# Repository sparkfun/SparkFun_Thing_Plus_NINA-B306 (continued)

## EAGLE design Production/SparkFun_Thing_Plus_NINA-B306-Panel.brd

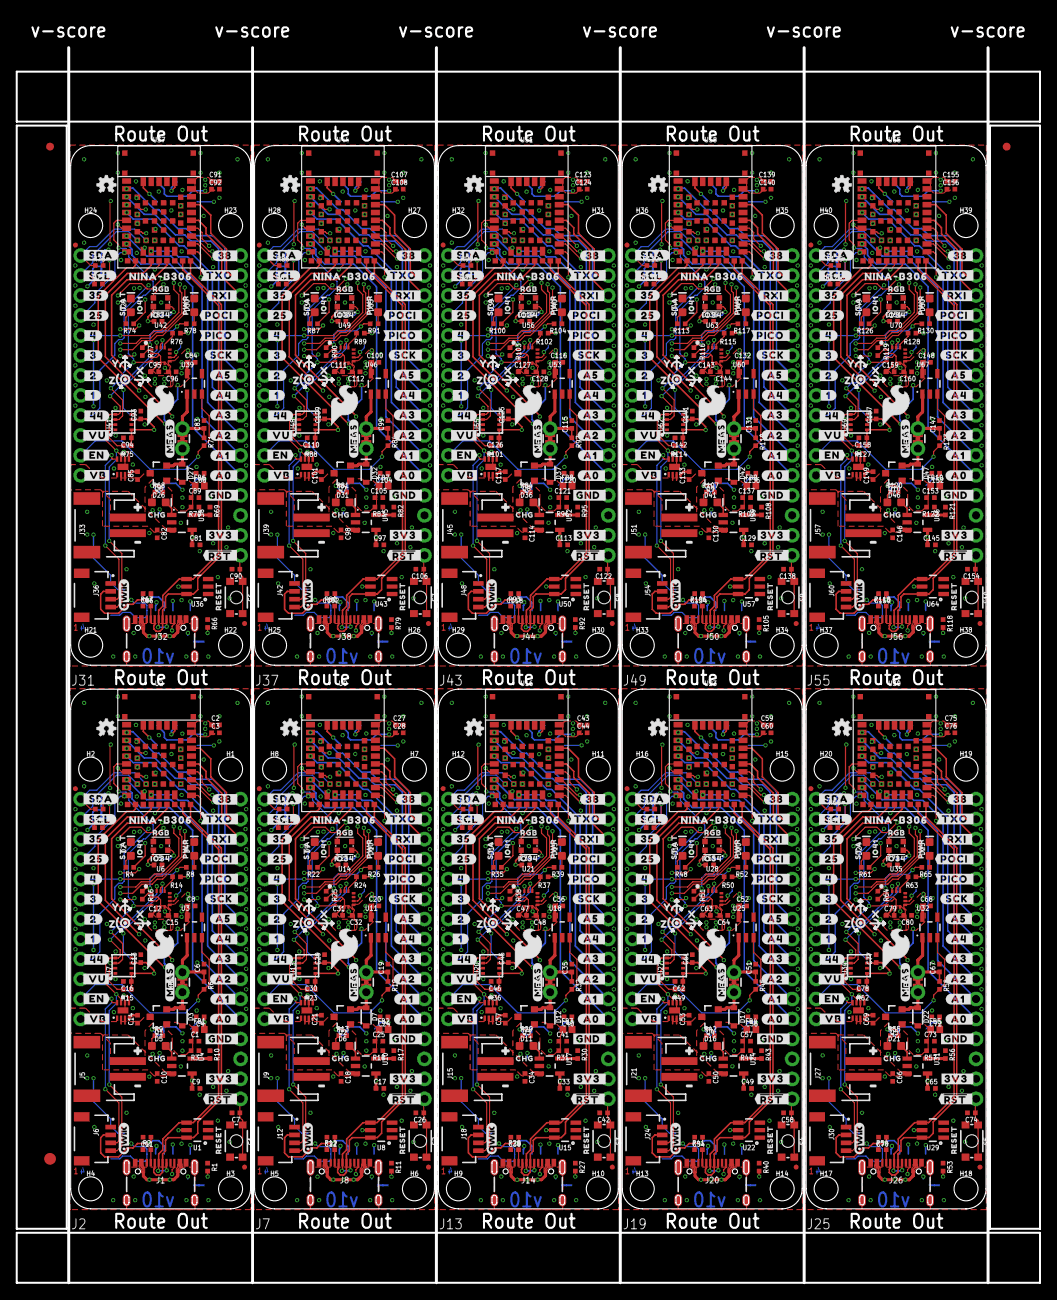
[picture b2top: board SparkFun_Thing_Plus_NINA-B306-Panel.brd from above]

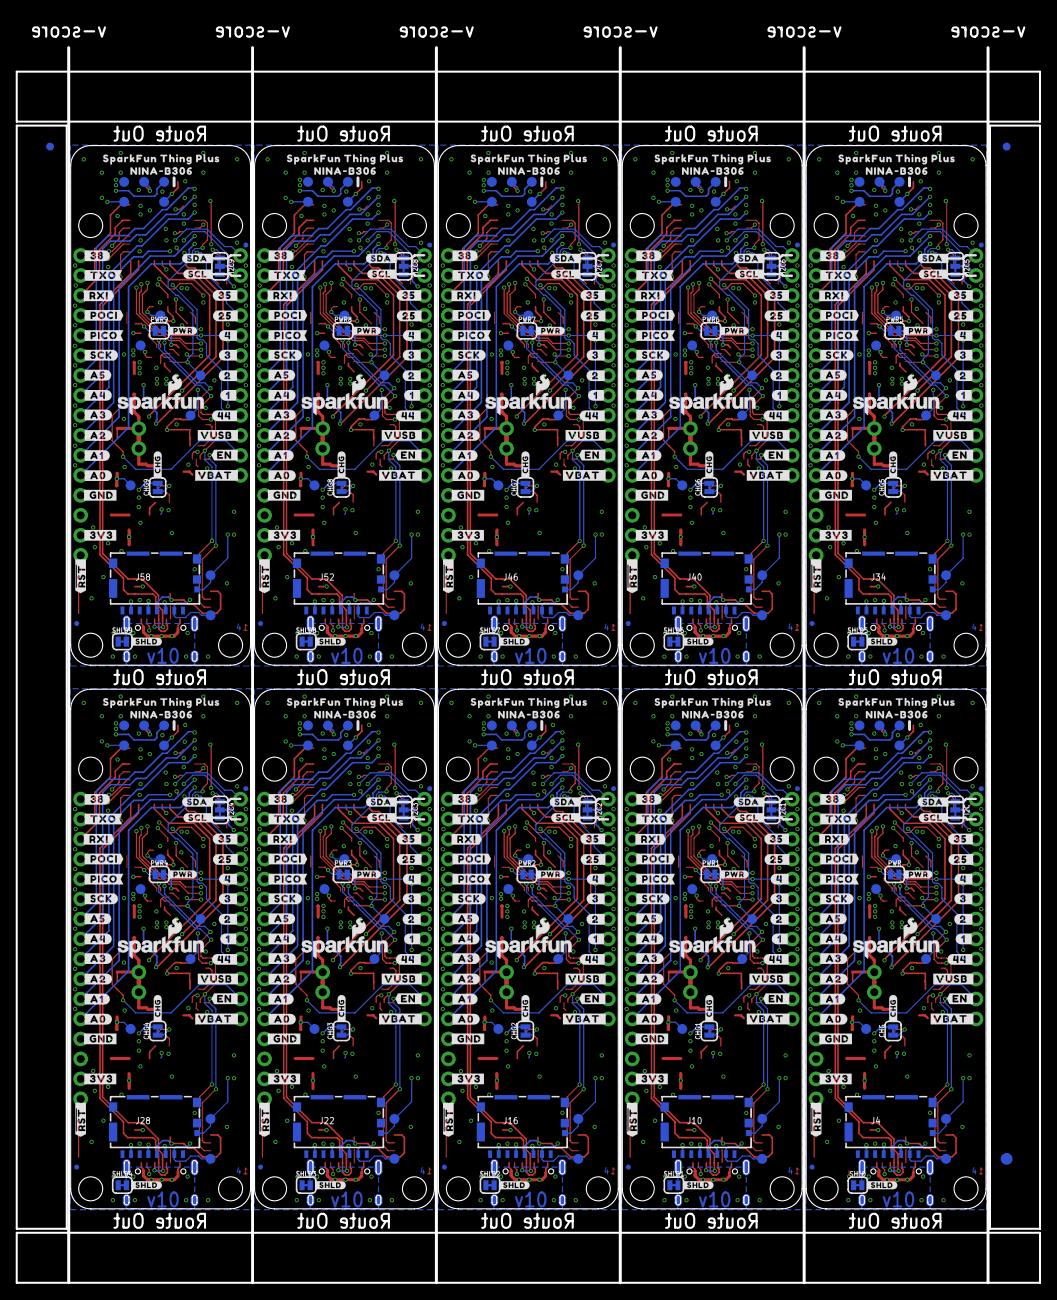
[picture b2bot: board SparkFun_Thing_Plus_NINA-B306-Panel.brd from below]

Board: 4 copper layers, 130.0 x 157.0 mm, 1506 parts (493 on the bottom side), 570 nets.

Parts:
C1, C4, C24, C25, C40, C41, C56, C57, C72, C73, C88, C89, C104, C105, C120, C121, C136, C137, C152, C153: 1.0nF; 0402-TIGHT
C2, C3, C5, C7, C12, C13, C14, C15, C16, C21, C23, C26, C27, C28, C29, C30, C31, C32, C37, C39, C42, C43, C44, C45, C46, C47, C48, C53, C55, C58, C59, C60, C61, C62, C63, C64, C69, C71, C74, C75, C76, C77, C78, C79, C80, C85, C87, C90, C91, C92, C93, C94, C95, C96, C101, C103, C106, C107, C108, C109, C110, C111, C112, C117, C119, C122, C123, C124, C125, C126, C127, C128, C133, C135, C138, C139, C140, C141, C142, C143, C144, C149, C151, C154, C155, C156, C157, C158, C159, C160: 0.1uF; 0402-TIGHT
C6, C19, C35, C51, C67, C83, C99, C115, C131, C147: 1.0uF; 0402-TIGHT
C8, C20, C36, C52, C68, C84, C100, C116, C132, C148: 2.2uF; 0402-TIGHT
C9, C10, C17, C18, C33, C34, C49, C50, C65, C66, C81, C82, C97, C98, C113, C114, C129, C130, C145, C146: 4.7uF; 0402-TIGHT
C11, C22, C38, C54, C70, C86, C102, C118, C134, C150: 10uF; 0402-TIGHT
CHG, CHG1, CHG2, CHG3, CHG4, CHG5, CHG6, CHG7, CHG8, CHG9: JUMPER-SMT_2_NC_TRACE_SILK; SMT-JUMPER_2_NC_TRACE_SILK
D1, D8, D13, D18, D23, D28, D33, D38, D43, D48: WS2812; WS2812-2020
D2, D9, D14, D19, D24, D29, D34, D39, D44, D49: BLUE; LED-0603
D3, D7, D12, D17, D22, D27, D32, D37, D42, D47: 3A/10V/280mV; SOD-323
D4, D10, D15, D20, D25, D30, D35, D40, D45, D50: RED; LED-0603
D5, D6, D11, D16, D21, D26, D31, D36, D41, D46: Yellow; LED-0603
E$1, E$2, E$3, E$4: FIDUCIAL-1X2
E$5, E$6: FIDUCIAL-1.5X3
FB1, FB2, FB3, FB4, FB5, FB6, FB7, FB8, FB9, FB10: 120Ω; 0402
FD1, FD2, FD3, FD4, FD5, FD6, FD7, FD8, FD9, FD10, FD11, FD12, FD13, FD14, FD15, FD16, FD17, FD18, FD19, FD20, FD21, FD22, FD23, FD24, FD25, FD26, FD27, FD28, FD29, FD30, FD31, FD32, FD33, FD34, FD35, FD36, FD37, FD38, FD39, FD40: FIDUCIALUFIDUCIAL; FIDUCIAL-MICRO
H1, H2, H3, H4, H5, H6, H7, H8, H9, H10, H11, H12, H13, H14, H15, H16, H17, H18, H19, H20, H21, H22, H23, H24, H25, H26, H27, H28, H29, H30, H31, H32, H33, H34, H35, H36, H37, H38, H39, H40: STAND-OFFTIGHT; STAND-OFF-TIGHT
I2C, I2C1, I2C2, I2C3, I2C4, I2C5, I2C6, I2C7, I2C8, I2C9: JUMPER-SMT_3_2-NC_TRACE_SILK; SMT-JUMPER_3_2-NC_TRACE_SILK
J1, J8, J14, J20, J26, J32, J38, J44, J50, J56: USB-C; USB-C-16P-4LAYER-ISOLATED
J2, J7, J13, J19, J25, J31, J37, J43, J49, J55: THING_PLUS_LOGICAL; THING_PLUS
J3, J11, J17, J23, J29, J35, J41, J47, J53, J59: CONN_03X2_NO4; PAD_05_03X2_TP_NO4
J4, J10, J16, J22, J28, J34, J40, J46, J52, J58: MICRO-SDFRICTION; MICROSD_TINY
J5, J9, J15, J21, J27, J33, J39, J45, J51, J57: JST-2-SMD
J6, J12, J18, J24, J30, J36, J42, J48, J54, J60: QWIIC_RA; JST04_1MM_RA
LOGO1, LOGO6, LOGO11, LOGO16, LOGO21, LOGO26, LOGO31, LOGO36, LOGO41, LOGO46: SFE_LOGO_NAME_FLAME.1_INCH; SFE_LOGO_NAME_FLAME_.1
LOGO2, LOGO10, LOGO15, LOGO20, LOGO25, LOGO30, LOGO35, LOGO40, LOGO45, LOGO50: FOUR_LAYER_WARNING
LOGO3, LOGO8, LOGO13, LOGO18, LOGO23, LOGO28, LOGO33, LOGO38, LOGO43, LOGO48: SPECIAL_INSTRUCTIONS-ORDERING; ORDERING_INSTRUCTIONS
LOGO4, LOGO9, LOGO14, LOGO19, LOGO24, LOGO29, LOGO34, LOGO39, LOGO44, LOGO49: QWIIC_LOGO_4MM; QWIIC_4MM
LOGO5, LOGO7, LOGO12, LOGO17, LOGO22, LOGO27, LOGO32, LOGO37, LOGO42, LOGO47: OSHW-LOGOMINI; OSHW-LOGO-MINI
MEAS, MEAS1, MEAS2, MEAS3, MEAS4, MEAS5, MEAS6, MEAS7, MEAS8, MEAS9: JUMPER-COMBO_2_NC_TRACE; COMBO-JUMPER_2_NC_TRACE
PWR, PWR1, PWR2, PWR3, PWR4, PWR5, PWR6, PWR7, PWR8, PWR9: JUMPER-SMT_2_NC_TRACE_SILK; SMT-JUMPER_2_NC_TRACE_SILK
Q1, Q2, Q3, Q4, Q5, Q6, Q7, Q8, Q9, Q10: 20V/4.2A/52mΩ/1.4W; SOT23-3
R1, R2, R11, R12, R27, R28, R40, R41, R53, R54, R66, R67, R79, R80, R92, R93, R105, R106, R118, R119: 5.1k; 0402-TIGHT
R3, R6, R14, R15, R16, R18, R19, R23, R24, R25, R31, R32, R36, R37, R38, R44, R45, R49, R50, R51, R57, R58, R62, R63, R64, R70, R71, R75, R76, R77, R83, R84, R88, R89, R90, R96, R97, R101, R102, R103, R109, R110, R114, R115, R116, R122, R123, R127, R128, R129: 10k; 0402-TIGHT
R4, R5, R7, R20, R21, R22, R33, R34, R35, R46, R47, R48, R59, R60, R61, R72, R73, R74, R85, R86, R87, R98, R99, R100, R111, R112, R113, R124, R125, R126: 2.2k; 0402-TIGHT
R8, R26, R39, R52, R65, R78, R91, R104, R117, R130: 1k; 0402-TIGHT
R9, R13, R29, R42, R55, R68, R81, R94, R107, R120: 4.7k; 0402-TIGHT
R10, R17, R30, R43, R56, R69, R82, R95, R108, R121: 2.0K; 0402-TIGHT
S1, S2, S3, S4, S5, S6, S7, S8, S9, S10: Reset; TACTILE_SWITCH_SMD_4.6X2.8MM
SHLD, SHLD1, SHLD2, SHLD3, SHLD4, SHLD5, SHLD6, SHLD7, SHLD8, SHLD9: SMT-JUMPER_2_NC_TRACE_SILK
TP1, TP2, TP3, TP4, TP5, TP6, TP7, TP8, TP9, TP10, TP11, TP12, TP13, TP14, TP15, TP16, TP17, TP18, TP19, TP20, TP21, TP22, TP23, TP24, TP25, TP26, TP27, TP28, TP29, TP30, TP31, TP32, TP33, TP34, TP35, TP36, TP37, TP38, TP39, TP40, TP41, TP42, TP43, TP44, TP45, TP46, TP47, TP48, TP49, TP50, TP51, TP52, TP53, TP54, TP55, TP56, TP57, TP58, TP59, TP60, TP61, TP62, TP63, TP64, TP65, TP66, TP67, TP68, TP69, TP70: TEST-POINT3X5; PAD.03X.05
U1, U8, U15, U22, U29, U36, U43, U50, U57, U64: ESD Diode; SOT-23-6
U2, U9, U16, U23, U30, U37, U44, U51, U58, U65: U-BLOX_NINA_B306; NINA_B306
U3, U11, U18, U25, U32, U39, U46, U53, U60, U67: XC6222B331MR-G; SOT23-5
U4, U10, U17, U24, U31, U38, U45, U52, U59, U66: MCP73831; SOT23-5
U5, U12, U19, U26, U33, U40, U47, U54, U61, U68: MAX17048; DFN-8
U6, U14, U21, U28, U35, U42, U49, U56, U63, U70: ISM330DHCX; LGA-14L
U7, U13, U20, U27, U34, U41, U48, U55, U62, U69: BME280; LGA-8-2.5X2.5
U$1, U$15, U$151, U$226, U$301, U$376, U$451, U$526, U$601, U$676: SFE_LOGO_FLAME_STOP_.1
U$2, U$77, U$152, U$227, U$302, U$377, U$452, U$527, U$602, U$677: SFE_LOGO_FLAME_.2
U$3, U$142, U$217, U$292, U$367, U$442, U$517, U$592, U$667, U$742: #_VU#0
U$4, U$78, U$153, U$228, U$303, U$378, U$453, U$528, U$603, U$678: #_EN#47
U$5, U$143, U$218, U$293, U$368, U$443, U$518, U$593, U$668, U$743: #3V3_#0
U$6, U$79, U$154, U$229, U$304, U$379, U$454, U$529, U$604, U$679: #_44#49
U$7, U$80, U$155, U$230, U$305, U$380, U$455, U$530, U$605, U$680: #_1#49
U$8, U$81, U$156, U$231, U$306, U$381, U$456, U$531, U$606, U$681: #_2#49
U$9, U$82, U$157, U$232, U$307, U$382, U$457, U$532, U$607, U$682: #_3#49
U$10, U$83, U$158, U$233, U$308, U$383, U$458, U$533, U$608, U$683: #_4#49
U$11, U$84, U$159, U$234, U$309, U$384, U$459, U$534, U$609, U$684: #_25#49
U$12, U$140, U$215, U$290, U$365, U$440, U$515, U$590, U$665, U$740: #_35#0
U$13, U$85, U$160, U$235, U$310, U$385, U$460, U$535, U$610, U$685: #_SCL#49
U$14, U$144, U$219, U$294, U$369, U$444, U$519, U$594, U$669, U$744: RESET0
U$16, U$86, U$161, U$236, U$311, U$386, U$461, U$536, U$611, U$686: #GND_#53
U$17, U$87, U$162, U$237, U$312, U$387, U$462, U$537, U$612, U$687: #A0_#54
U$18, U$88, U$163, U$238, U$313, U$388, U$463, U$538, U$613, U$688: #A1_#54
U$19, U$89, U$164, U$239, U$314, U$389, U$464, U$539, U$614, U$689: #A2_#54
U$20, U$90, U$165, U$240, U$315, U$390, U$465, U$540, U$615, U$690: #A3_#54
U$21, U$91, U$166, U$241, U$316, U$391, U$466, U$541, U$616, U$691: #A4_#54
U$22, U$92, U$167, U$242, U$317, U$392, U$467, U$542, U$617, U$692: #A5_#54
U$23, U$93, U$168, U$243, U$318, U$393, U$468, U$543, U$618, U$693: #SCK_#54
U$24, U$97, U$172, U$247, U$322, U$397, U$472, U$547, U$622, U$697: #PICO_#60
U$25, U$98, U$173, U$248, U$323, U$398, U$473, U$548, U$623, U$698: #POCI_#61
U$26, U$94, U$169, U$244, U$319, U$394, U$469, U$544, U$619, U$694: #TXO_#57
U$27, U$95, U$170, U$245, U$320, U$395, U$470, U$545, U$620, U$695: #RXI_#59
U$28, U$96, U$171, U$246, U$321, U$396, U$471, U$546, U$621, U$696: #38_#60
U$29, U$99, U$174, U$249, U$324, U$399, U$474, U$549, U$624, U$699: #_SDA#68
U$30, U$127, U$202, U$277, U$352, U$427, U$502, U$577, U$652, U$727: #_CHG#30707
U$31, U$147, U$222, U$297, U$372, U$447, U$522, U$597, U$672, U$747: #_3V3#0
U$32, U$100, U$175, U$250, U$325, U$400, U$475, U$550, U$625, U$700: #_GND#70
U$33, U$101, U$176, U$251, U$326, U$401, U$476, U$551, U$626, U$701: #_A0#71
U$34, U$102, U$177, U$252, U$327, U$402, U$477, U$552, U$627, U$702: #_A1#71
U$35, U$103, U$178, U$253, U$328, U$403, U$478, U$553, U$628, U$703: #_A2#71
U$36, U$104, U$179, U$254, U$329, U$404, U$479, U$554, U$629, U$704: #_A3#71
U$37, U$105, U$180, U$255, U$330, U$405, U$480, U$555, U$630, U$705: #_A4#71
U$38, U$106, U$181, U$256, U$331, U$406, U$481, U$556, U$631, U$706: #_A5#71
U$39, U$107, U$182, U$257, U$332, U$407, U$482, U$557, U$632, U$707: #_SCK#71
U$40, U$108, U$183, U$258, U$333, U$408, U$483, U$558, U$633, U$708: #_PICO#72
U$41, U$109, U$184, U$259, U$334, U$409, U$484, U$559, U$634, U$709: #_POCI#73
U$42, U$110, U$185, U$260, U$335, U$410, U$485, U$560, U$635, U$710: #_TXO#74
U$43, U$111, U$186, U$261, U$336, U$411, U$486, U$561, U$636, U$711: #_RXI#75
U$44, U$112, U$187, U$262, U$337, U$412, U$487, U$562, U$637, U$712: #_38#76
U$45, U$139, U$214, U$289, U$364, U$439, U$514, U$589, U$664, U$739: #35_#0
U$46, U$113, U$188, U$263, U$338, U$413, U$488, U$563, U$638, U$713: #25_#79
U$47, U$114, U$189, U$264, U$339, U$414, U$489, U$564, U$639, U$714: #4_#79
U$48, U$115, U$190, U$265, U$340, U$415, U$490, U$565, U$640, U$715: #3_#79
U$49, U$116, U$191, U$266, U$341, U$416, U$491, U$566, U$641, U$716: #2_#79
U$50, U$117, U$192, U$267, U$342, U$417, U$492, U$567, U$642, U$717: #1_#79
U$51, U$118, U$193, U$268, U$343, U$418, U$493, U$568, U$643, U$718: #44_#79
U$52, U$146, U$221, U$296, U$371, U$446, U$521, U$596, U$671, U$746: #VBAT_#0
U$53, U$119, U$194, U$269, U$344, U$419, U$494, U$569, U$644, U$719: #EN_#80
U$54, U$74, U$138, U$148, U$213, U$223, U$288, U$298, U$363, U$373, U$438, U$448, U$513, U$523, U$588, U$598, U$663, U$673, U$738, U$748: ##RST#_#0
U$55, U$120, U$195, U$270, U$345, U$420, U$495, U$570, U$645, U$720: #SDA_#82
U$56, U$121, U$196, U$271, U$346, U$421, U$496, U$571, U$646, U$721: #SCL_#85
U$57, U$122, U$197, U$272, U$347, U$422, U$497, U$572, U$647, U$722: #_PWR#90
U$58, U$145, U$220, U$295, U$370, U$445, U$520, U$595, U$670, U$745: #VUSB_#0
U$59, U$123, U$198, U$273, U$348, U$423, U$498, U$573, U$648, U$723: #_SHLD#93
U$60, U$124, U$199, U$274, U$349, U$424, U$499, U$574, U$649, U$724: SPARKFUN_THING_PLUS96
U$61, U$125, U$200, U$275, U$350, U$425, U$500, U$575, U$650, U$725: NINA#B30697
U$62, U$126, U$201, U$276, U$351, U$426, U$501, U$576, U$651, U$726: #MEAS#30701
U$63, U$141, U$216, U$291, U$366, U$441, U$516, U$591, U$666, U$741: #_VB#0
U$64, U$128, U$203, U$278, U$353, U$428, U$503, U$578, U$653, U$728: RGB30710
U$65, U$129, U$204, U$279, U$354, U$429, U$504, U$579, U$654, U$729: STAT30711
U$66, U$130, U$205, U$280, U$355, U$430, U$505, U$580, U$655, U$730: PWR30712
U$67, U$131, U$206, U$281, U$356, U$431, U$506, U$581, U$656, U$731: NINA#B30630713
U$68, U$132, U$207, U$282, U$357, U$432, U$507, U$582, U$657, U$732: X2114
U$69, U$133, U$208, U$283, U$358, U$433, U$508, U$583, U$658, U$733: Y2115
U$70, U$134, U$209, U$284, U$359, U$434, U$509, U$584, U$659, U$734: Z2116
U$71, U$135, U$210, U$285, U$360, U$435, U$510, U$585, U$660, U$735: IO414130630715
U$72, U$136, U$211, U$286, U$361, U$436, U$511, U$586, U$661, U$736: IO34414130630716
U$73, U$137, U$212, U$287, U$362, U$437, U$512, U$587, U$662, U$737: CHG0
U$75, U$149, U$224, U$299, U$374, U$449, U$524, U$599, U$674, U$749: #3
U$76, U$150, U$225, U$300, U$375, U$450, U$525, U$600, U$675, U$750: #4

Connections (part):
3.3V: C2.1, C3.1, C5.1, C8.1, C11.1, C12.1, C13.1, C15.1, C16.1, D1.VCC, I2C.2, J2.27, J3.1, J4.4, J6.2, PWR.2, R14.1, R15.1, R16.1, U2.9, U2.10, U3.5, U6.P5, U6.P8, U7.6, U7.8
3.3V1: C20.1, C22.1, C23.1, C27.1, C28.1, C29.1, C30.1, C31.1, C32.1, D8.VCC, I2C1.2, J7.27, J10.4, J11.1, J12.2, PWR1.2, R23.1, R24.1, R25.1, U9.9, U9.10, U11.5, U13.6, U13.8, U14.P5, U14.P8
3.3V2: C36.1, C38.1, C39.1, C43.1, C44.1, C45.1, C46.1, C47.1, C48.1, D13.VCC, I2C2.2, J13.27, J16.4, J17.1, J18.2, PWR2.2, R36.1, R37.1, R38.1, U16.9, U16.10, U18.5, U20.6, U20.8, U21.P5, U21.P8
3.3V3: C52.1, C54.1, C55.1, C59.1, C60.1, C61.1, C62.1, C63.1, C64.1, D18.VCC, I2C3.2, J19.27, J22.4, J23.1, J24.2, PWR3.2, R49.1, R50.1, R51.1, U23.9, U23.10, U25.5, U27.6, U27.8, U28.P5, U28.P8
3.3V4: C68.1, C70.1, C71.1, C75.1, C76.1, C77.1, C78.1, C79.1, C80.1, D23.VCC, I2C4.2, J25.27, J28.4, J29.1, J30.2, PWR4.2, R62.1, R63.1, R64.1, U30.9, U30.10, U32.5, U34.6, U34.8, U35.P5, U35.P8
3.3V5: C84.1, C86.1, C87.1, C91.1, C92.1, C93.1, C94.1, C95.1, C96.1, D28.VCC, I2C5.2, J31.27, J34.4, J35.1, J36.2, PWR5.2, R75.1, R76.1, R77.1, U37.9, U37.10, U39.5, U41.6, U41.8, U42.P5, U42.P8
3.3V6: C100.1, C102.1, C103.1, C107.1, C108.1, C109.1, C110.1, C111.1, C112.1, D33.VCC, I2C6.2, J37.27, J40.4, J41.1, J42.2, PWR6.2, R88.1, R89.1, R90.1, U44.9, U44.10, U46.5, U48.6, U48.8, U49.P5, U49.P8
3.3V7: C116.1, C118.1, C119.1, C123.1, C124.1, C125.1, C126.1, C127.1, C128.1, D38.VCC, I2C7.2, J43.27, J46.4, J47.1, J48.2, PWR7.2, R101.1, R102.1, R103.1, U51.9, U51.10, U53.5, U55.6, U55.8, U56.P5, U56.P8
3.3V8: C132.1, C134.1, C135.1, C139.1, C140.1, C141.1, C142.1, C143.1, C144.1, D43.VCC, I2C8.2, J49.27, J52.4, J53.1, J54.2, PWR8.2, R114.1, R115.1, R116.1, U58.9, U58.10, U60.5, U62.6, U62.8, U63.P5, U63.P8
3.3V9: C148.1, C150.1, C151.1, C155.1, C156.1, C157.1, C158.1, C159.1, C160.1, D48.VCC, I2C9.2, J55.27, J58.4, J59.1, J60.2, PWR9.2, R127.1, R128.1, R129.1, U65.9, U65.10, U67.5, U69.6, U69.8, U70.P5, U70.P8
!RESET!: C7.1, J2.28, J3.6, S1.3, S1.4, U2.19
!RESET!1: C26.1, J7.28, J11.6, S2.3, S2.4, U9.19
!RESET!2: C42.1, J13.28, J17.6, S3.3, S3.4, U16.19
!RESET!3: C58.1, J19.28, J23.6, S4.3, S4.4, U23.19
!RESET!4: C74.1, J25.28, J29.6, S5.3, S5.4, U30.19
!RESET!5: C90.1, J31.28, J35.6, S6.3, S6.4, U37.19
!RESET!6: C106.1, J37.28, J41.6, S7.3, S7.4, U44.19
!RESET!7: C122.1, J43.28, J47.6, S8.3, S8.4, U51.19
!RESET!8: C138.1, J49.28, J53.6, S9.3, S9.4, U58.19
!RESET!9: C154.1, J55.28, J59.6, S10.3, S10.4, U65.19
EN: J2.11, R6.2, U3.3
EN1: J7.11, R19.2, U11.3
EN2: J13.11, R32.2, U18.3
EN3: J19.11, R45.2, U25.3
EN4: J25.11, R58.2, U32.3
EN5: J31.11, R71.2, U39.3
EN6: J37.11, R84.2, U46.3
EN7: J43.11, R97.2, U53.3
EN8: J49.11, R110.2, U60.3
EN9: J55.11, R123.2, U67.3
GND: C1.2, C2.2, C3.2, C4.2, C5.2, C6.2, C7.2, C8.2, C9.2, C10.2, C11.2, C12.2, C13.2, C14.2, C15.2, C16.2, D1.GND, D2.C, D4.C, J1.GND, J1.GND2, J2.25, J3.5, J4.6, J4.GND1, J4.GND2, J4.GND3, J4.GND4, J4.GND5, J4.GND6, J5.1, J6.1, R1.1, R2.1, R3.1, R10.1, S1.1, S1.2, SHLD.1, U1.2, U2.6, U2.12, U2.14, U2.26, U2.30, U2.53, U2.56, U2.57, U2.58, U2.59, U2.60, U2.61, U2.62, U2.63, U2.64, U2.65, U2.66, U2.67, U2.68, U2.69, U2.70, U2.71, U3.2, U4.2, U5.1, U5.4, U5.6, U5.9, U6.P2, U6.P3, U6.P6, U6.P7, U7.1, U7.5, U7.7
GND1: C17.2, C18.2, C19.2, C20.2, C21.2, C22.2, C23.2, C24.2, C25.2, C26.2, C27.2, C28.2, C29.2, C30.2, C31.2, C32.2, D8.GND, D9.C, D10.C, J7.25, J8.GND, J8.GND2, J9.1, J10.6, J10.GND1, J10.GND2, J10.GND3, J10.GND4, J10.GND5, J10.GND6, J11.5, J12.1, R11.1, R12.1, R17.1, R18.1, S2.1, S2.2, SHLD1.1, U8.2, U9.6, U9.12, U9.14, U9.26, U9.30, U9.53, U9.56, U9.57, U9.58, U9.59, U9.60, U9.61, U9.62, U9.63, U9.64, U9.65, U9.66, U9.67, U9.68, U9.69, U9.70, U9.71, U10.2, U11.2, U12.1, U12.4, U12.6, U12.9, U13.1, U13.5, U13.7, U14.P2, U14.P3, U14.P6, U14.P7
GND2: C33.2, C34.2, C35.2, C36.2, C37.2, C38.2, C39.2, C40.2, C41.2, C42.2, C43.2, C44.2, C45.2, C46.2, C47.2, C48.2, D13.GND, D14.C, D15.C, J13.25, J14.GND, J14.GND2, J15.1, J16.6, J16.GND1, J16.GND2, J16.GND3, J16.GND4, J16.GND5, J16.GND6, J17.5, J18.1, R27.1, R28.1, R30.1, R31.1, S3.1, S3.2, SHLD2.1, U15.2, U16.6, U16.12, U16.14, U16.26, U16.30, U16.53, U16.56, U16.57, U16.58, U16.59, U16.60, U16.61, U16.62, U16.63, U16.64, U16.65, U16.66, U16.67, U16.68, U16.69, U16.70, U16.71, U17.2, U18.2, U19.1, U19.4, U19.6, U19.9, U20.1, U20.5, U20.7, U21.P2, U21.P3, U21.P6, U21.P7
GND3: C49.2, C50.2, C51.2, C52.2, C53.2, C54.2, C55.2, C56.2, C57.2, C58.2, C59.2, C60.2, C61.2, C62.2, C63.2, C64.2, D18.GND, D19.C, D20.C, J19.25, J20.GND, J20.GND2, J21.1, J22.6, J22.GND1, J22.GND2, J22.GND3, J22.GND4, J22.GND5, J22.GND6, J23.5, J24.1, R40.1, R41.1, R43.1, R44.1, S4.1, S4.2, SHLD3.1, U22.2, U23.6, U23.12, U23.14, U23.26, U23.30, U23.53, U23.56, U23.57, U23.58, U23.59, U23.60, U23.61, U23.62, U23.63, U23.64, U23.65, U23.66, U23.67, U23.68, U23.69, U23.70, U23.71, U24.2, U25.2, U26.1, U26.4, U26.6, U26.9, U27.1, U27.5, U27.7, U28.P2, U28.P3, U28.P6, U28.P7
GND4: C65.2, C66.2, C67.2, C68.2, C69.2, C70.2, C71.2, C72.2, C73.2, C74.2, C75.2, C76.2, C77.2, C78.2, C79.2, C80.2, D23.GND, D24.C, D25.C, J25.25, J26.GND, J26.GND2, J27.1, J28.6, J28.GND1, J28.GND2, J28.GND3, J28.GND4, J28.GND5, J28.GND6, J29.5, J30.1, R53.1, R54.1, R56.1, R57.1, S5.1, S5.2, SHLD4.1, U29.2, U30.6, U30.12, U30.14, U30.26, U30.30, U30.53, U30.56, U30.57, U30.58, U30.59, U30.60, U30.61, U30.62, U30.63, U30.64, U30.65, U30.66, U30.67, U30.68, U30.69, U30.70, U30.71, U31.2, U32.2, U33.1, U33.4, U33.6, U33.9, U34.1, U34.5, U34.7, U35.P2, U35.P3, U35.P6, U35.P7
GND5: C81.2, C82.2, C83.2, C84.2, C85.2, C86.2, C87.2, C88.2, C89.2, C90.2, C91.2, C92.2, C93.2, C94.2, C95.2, C96.2, D28.GND, D29.C, D30.C, J31.25, J32.GND, J32.GND2, J33.1, J34.6, J34.GND1, J34.GND2, J34.GND3, J34.GND4, J34.GND5, J34.GND6, J35.5, J36.1, R66.1, R67.1, R69.1, R70.1, S6.1, S6.2, SHLD5.1, U36.2, U37.6, U37.12, U37.14, U37.26, U37.30, U37.53, U37.56, U37.57, U37.58, U37.59, U37.60, U37.61, U37.62, U37.63, U37.64, U37.65, U37.66, U37.67, U37.68, U37.69, U37.70, U37.71, U38.2, U39.2, U40.1, U40.4, U40.6, U40.9, U41.1, U41.5, U41.7, U42.P2, U42.P3, U42.P6, U42.P7
GND6: C97.2, C98.2, C99.2, C100.2, C101.2, C102.2, C103.2, C104.2, C105.2, C106.2, C107.2, C108.2, C109.2, C110.2, C111.2, C112.2, D33.GND, D34.C, D35.C, J37.25, J38.GND, J38.GND2, J39.1, J40.6, J40.GND1, J40.GND2, J40.GND3, J40.GND4, J40.GND5, J40.GND6, J41.5, J42.1, R79.1, R80.1, R82.1, R83.1, S7.1, S7.2, SHLD6.1, U43.2, U44.6, U44.12, U44.14, U44.26, U44.30, U44.53, U44.56, U44.57, U44.58, U44.59, U44.60, U44.61, U44.62, U44.63, U44.64, U44.65, U44.66, U44.67, U44.68, U44.69, U44.70, U44.71, U45.2, U46.2, U47.1, U47.4, U47.6, U47.9, U48.1, U48.5, U48.7, U49.P2, U49.P3, U49.P6, U49.P7
GND7: C113.2, C114.2, C115.2, C116.2, C117.2, C118.2, C119.2, C120.2, C121.2, C122.2, C123.2, C124.2, C125.2, C126.2, C127.2, C128.2, D38.GND, D39.C, D40.C, J43.25, J44.GND, J44.GND2, J45.1, J46.6, J46.GND1, J46.GND2, J46.GND3, J46.GND4, J46.GND5, J46.GND6, J47.5, J48.1, R92.1, R93.1, R95.1, R96.1, S8.1, S8.2, SHLD7.1, U50.2, U51.6, U51.12, U51.14, U51.26, U51.30, U51.53, U51.56, U51.57, U51.58, U51.59, U51.60, U51.61, U51.62, U51.63, U51.64, U51.65, U51.66, U51.67, U51.68, U51.69, U51.70, U51.71, U52.2, U53.2, U54.1, U54.4, U54.6, U54.9, U55.1, U55.5, U55.7, U56.P2, U56.P3, U56.P6, U56.P7
GND8: C129.2, C130.2, C131.2, C132.2, C133.2, C134.2, C135.2, C136.2, C137.2, C138.2, C139.2, C140.2, C141.2, C142.2, C143.2, C144.2, D43.GND, D44.C, D45.C, J49.25, J50.GND, J50.GND2, J51.1, J52.6, J52.GND1, J52.GND2, J52.GND3, J52.GND4, J52.GND5, J52.GND6, J53.5, J54.1, R105.1, R106.1, R108.1, R109.1, S9.1, S9.2, SHLD8.1, U57.2, U58.6, U58.12, U58.14, U58.26, U58.30, U58.53, U58.56, U58.57, U58.58, U58.59, U58.60, U58.61, U58.62, U58.63, U58.64, U58.65, U58.66, U58.67, U58.68, U58.69, U58.70, U58.71, U59.2, U60.2, U61.1, U61.4, U61.6, U61.9, U62.1, U62.5, U62.7, U63.P2, U63.P3, U63.P6, U63.P7
GND9: C145.2, C146.2, C147.2, C148.2, C149.2, C150.2, C151.2, C152.2, C153.2, C154.2, C155.2, C156.2, C157.2, C158.2, C159.2, C160.2, D48.GND, D49.C, D50.C, J55.25, J56.GND, J56.GND2, J57.1, J58.6, J58.GND1, J58.GND2, J58.GND3, J58.GND4, J58.GND5, J58.GND6, J59.5, J60.1, R118.1, R119.1, R121.1, R122.1, S10.1, S10.2, SHLD9.1, U64.2, U65.6, U65.12, U65.14, U65.26, U65.30, U65.53, U65.56, U65.57, U65.58, U65.59, U65.60, U65.61, U65.62, U65.63, U65.64, U65.65, U65.66, U65.67, U65.68, U65.69, U65.70, U65.71, U66.2, U67.2, U68.1, U68.4, U68.6, U68.9, U69.1, U69.5, U69.7, U70.P2, U70.P3, U70.P6, U70.P7
IO1/GPIO1: J2.8, U2.1
IO1/GPIO2: J7.8, U9.1
IO1/GPIO3: J13.8, U16.1
IO1/GPIO4: J19.8, U23.1
IO1/GPIO5: J25.8, U30.1
IO1/GPIO6: J31.8, U37.1
IO1/GPIO7: J37.8, U44.1
IO1/GPIO8: J43.8, U51.1
IO1/GPIO9: J49.8, U58.1
IO1/GPIO10: J55.8, U65.1
IO2/GPIO1: J7.7, U9.2
IO2/GPIO2: J2.7, U2.2
IO2/GPIO3: J13.7, U16.2
IO2/GPIO4: J19.7, U23.2
IO2/GPIO5: J25.7, U30.2
IO2/GPIO6: J31.7, U37.2
IO2/GPIO7: J37.7, U44.2
IO2/GPIO8: J43.7, U51.2
IO2/GPIO9: J49.7, U58.2
IO2/GPIO10: J55.7, U65.2
IO3/GPIO1: J7.6, U9.3
IO3/GPIO2: J13.6, U16.3
IO3/GPIO3: J2.6, U2.3
IO3/GPIO4: J19.6, U23.3
IO3/GPIO5: J25.6, U30.3
IO3/GPIO6: J31.6, U37.3
IO3/GPIO7: J37.6, U44.3
IO3/GPIO8: J43.6, U51.3
IO3/GPIO9: J49.6, U58.3
IO3/GPIO10: J55.6, U65.3
IO4/GPIO1: J7.5, U9.4
IO4/GPIO2: J13.5, U16.4
IO4/GPIO3: J19.5, U23.4
IO4/GPIO4: J2.5, U2.4
IO4/GPIO5: J25.5, U30.4
IO4/GPIO6: J31.5, U37.4
IO4/GPIO7: J37.5, U44.4
IO4/GPIO8: J43.5, U51.4
IO4/GPIO9: J49.5, U58.4
IO4/GPIO10: J55.5, U65.4
IO5/NINA_RX/DEV_TX: J2.15, U2.5
IO5/NINA_RX/DEV_TX1: J7.15, U9.5
IO5/NINA_RX/DEV_TX2: J13.15, U16.5
IO5/NINA_RX/DEV_TX3: J19.15, U23.5
IO5/NINA_RX/DEV_TX4: J25.15, U30.5
IO5/NINA_RX/DEV_TX5: J31.15, U37.5
IO5/NINA_RX/DEV_TX6: J37.15, U44.5
IO5/NINA_RX/DEV_TX7: J43.15, U51.5
IO5/NINA_RX/DEV_TX8: J49.15, U58.5
IO5/NINA_RX/DEV_TX9: J55.15, U65.5
IO7/NINA_TX/DEV_RX: J2.14, U2.7
IO7/NINA_TX/DEV_RX1: J7.14, U9.7
IO7/NINA_TX/DEV_RX2: J13.14, U16.7
IO7/NINA_TX/DEV_RX3: J19.14, U23.7
IO7/NINA_TX/DEV_RX4: J25.14, U30.7
IO7/NINA_TX/DEV_RX5: J31.14, U37.7
IO7/NINA_TX/DEV_RX6: J37.14, U44.7
IO7/NINA_TX/DEV_RX7: J43.14, U51.7
IO7/NINA_TX/DEV_RX8: J49.14, U58.7
IO7/NINA_TX/DEV_RX9: J55.14, U65.7
IO17/A1: J7.19, U9.17
IO17/A2: J13.19, U16.17
IO17/A3: J19.19, U23.17
IO17/A4: J25.19, U30.17
IO17/A5: J2.19, U2.17
IO17/A6: J31.19, U37.17
IO17/A7: J37.19, U44.17
IO17/A8: J43.19, U51.17
IO17/A9: J49.19, U58.17
IO17/A10: J55.19, U65.17
IO18/A1: J7.20, U9.18
IO18/A2: J13.20, U16.18
IO18/A3: J19.20, U23.18
IO18/A4: J2.20, U2.18
IO18/A5: J25.20, U30.18
IO18/A6: J31.20, U37.18
IO18/A7: J37.20, U44.18
IO18/A8: J43.20, U51.18
IO18/A9: J49.20, U58.18
IO18/A10: J55.20, U65.18
IO20/A1: J7.21, U9.20
IO20/A2: J13.21, U16.20
IO20/A3: J2.21, U2.20
IO20/A4: J19.21, U23.20
IO20/A5: J25.21, U30.20
IO20/A6: J31.21, U37.20
IO20/A7: J37.21, U44.20
IO20/A8: J43.21, U51.20
IO20/A9: J49.21, U58.20
IO20/A10: J55.21, U65.20
IO21/IMU_INT1: TP8.1, U2.21, U6.P4
IO21/IMU_INT2: TP11.1, U9.21, U14.P4
IO21/IMU_INT3: TP18.1, U16.21, U21.P4
IO21/IMU_INT4: TP25.1, U23.21, U28.P4
IO21/IMU_INT5: TP32.1, U30.21, U35.P4
IO21/IMU_INT6: TP39.1, U37.21, U42.P4
IO21/IMU_INT7: TP46.1, U44.21, U49.P4
IO21/IMU_INT8: TP53.1, U51.21, U56.P4
IO21/IMU_INT9: TP60.1, U58.21, U63.P4
IO21/IMU_INT10: TP67.1, U65.21, U70.P4
IO22/IMU_INT1: TP12.1, U9.22, U14.P9
IO22/IMU_INT2: TP9.1, U2.22, U6.P9
IO22/IMU_INT3: TP19.1, U16.22, U21.P9
IO22/IMU_INT4: TP26.1, U23.22, U28.P9
IO22/IMU_INT5: TP33.1, U30.22, U35.P9
IO22/IMU_INT6: TP40.1, U37.22, U42.P9
IO22/IMU_INT7: TP47.1, U44.22, U49.P9
IO22/IMU_INT8: TP54.1, U51.22, U56.P9
IO22/IMU_INT9: TP61.1, U58.22, U63.P9
IO22/IMU_INT10: TP68.1, U65.22, U70.P9
IO23/A1: J2.23, U2.23
IO23/A2: J7.23, U9.23
IO23/A3: J13.23, U16.23
IO23/A4: J19.23, U23.23
IO23/A5: J25.23, U30.23
IO23/A6: J31.23, U37.23
IO23/A7: J37.23, U44.23
IO23/A8: J43.23, U51.23
IO23/A9: J49.23, U58.23
IO23/A10: J55.23, U65.23
IO24/A0: J2.24, U2.24
IO24/A1: J7.24, U9.24
IO24/A2: J13.24, U16.24
IO24/A3: J19.24, U23.24
IO24/A4: J25.24, U30.24
IO24/A5: J31.24, U37.24
IO24/A6: J37.24, U44.24
IO24/A7: J43.24, U51.24
IO24/A8: J49.24, U58.24
IO24/A9: J55.24, U65.24
IO25/GPIO1: J7.4, U9.25
IO25/GPIO2: J13.4, U16.25
IO25/GPIO3: J19.4, U23.25
IO25/GPIO4: J25.4, U30.25
IO25/GPIO5: J2.4, U2.25
IO25/GPIO6: J31.4, U37.25
IO25/GPIO7: J37.4, U44.25
IO25/GPIO8: J43.4, U51.25
IO25/GPIO9: J49.4, U58.25
IO25/GPIO10: J55.4, U65.25
IO27/A1: J7.22, U9.27
IO27/A2: J2.22, U2.27
IO27/A3: J13.22, U16.27
IO27/A4: J19.22, U23.27
IO27/A5: J25.22, U30.27
IO27/A6: J31.22, U37.27
IO27/A7: J37.22, U44.27
IO27/A8: J43.22, U51.27
IO27/A9: J49.22, U58.27
IO27/A10: J55.22, U65.27
IO34/RGB: D1.DI, U2.34
IO34/RGB1: D8.DI, U9.34
IO34/RGB2: D13.DI, U16.34
IO34/RGB3: D18.DI, U23.34
IO34/RGB4: D23.DI, U30.34
IO34/RGB5: D28.DI, U37.34
IO34/RGB6: D33.DI, U44.34
IO34/RGB7: D38.DI, U51.34
IO34/RGB8: D43.DI, U58.34
IO34/RGB9: D48.DI, U65.34
IO35/GPIO1: J7.3, U9.35
IO35/GPIO2: J13.3, U16.35
IO35/GPIO3: J19.3, U23.35
IO35/GPIO4: J25.3, U30.35
IO35/GPIO5: J31.3, U37.35
IO35/GPIO6: J2.3, U2.35
IO35/GPIO7: J37.3, U44.35
IO35/GPIO8: J43.3, U51.35
IO35/GPIO9: J49.3, U58.35
IO35/GPIO10: J55.3, U65.35
IO37/SD_DET: J4.9, TP4.1, U2.37
IO37/SD_DET1: J10.9, TP10.1, U9.37
IO37/SD_DET2: J16.9, TP17.1, U16.37
IO37/SD_DET3: J22.9, TP24.1, U23.37
IO37/SD_DET4: J28.9, TP31.1, U30.37
IO37/SD_DET5: J34.9, TP38.1, U37.37
IO37/SD_DET6: J40.9, TP45.1, U44.37
IO37/SD_DET7: J46.9, TP52.1, U51.37
IO37/SD_DET8: J52.9, TP59.1, U58.37
IO37/SD_DET9: J58.9, TP66.1, U65.37
IO38/FREE: J2.13, U2.38
IO38/FREE1: J7.13, U9.38
IO38/FREE2: J13.13, U16.38
IO38/FREE3: J19.13, U23.38
IO38/FREE4: J25.13, U30.38
IO38/FREE5: J31.13, U37.38
IO38/FREE6: J37.13, U44.38
IO38/FREE7: J43.13, U51.38
IO38/FREE8: J49.13, U58.38
IO38/FREE9: J55.13, U65.38
IO39/!BATT_ALRT!: TP7.1, U2.39, U5.5
IO39/!BATT_ALRT!1: TP13.1, U9.39, U12.5
IO39/!BATT_ALRT!2: TP20.1, U16.39, U19.5
IO39/!BATT_ALRT!3: TP27.1, U23.39, U26.5
IO39/!BATT_ALRT!4: TP34.1, U30.39, U33.5
IO39/!BATT_ALRT!5: TP41.1, U37.39, U40.5
IO39/!BATT_ALRT!6: TP48.1, U44.39, U47.5
IO39/!BATT_ALRT!7: TP55.1, U51.39, U54.5
IO39/!BATT_ALRT!8: TP62.1, U58.39, U61.5
IO39/!BATT_ALRT!9: TP69.1, U65.39, U68.5
IO41/LED: R4.1, U2.41
IO41/LED1: R22.1, U9.41
IO41/LED2: R35.1, U16.41
IO41/LED3: R48.1, U23.41
IO41/LED4: R61.1, U30.41
IO41/LED5: R74.1, U37.41
IO41/LED6: R87.1, U44.41
IO41/LED7: R100.1, U51.41
IO41/LED8: R113.1, U58.41
IO41/LED9: R126.1, U65.41
IO42/SCL: J2.2, J6.4, R5.1, U2.42, U5.7, U6.P13, U7.4
IO42/SCL1: J7.2, J12.4, R20.1, U9.42, U12.7, U13.4, U14.P13
IO42/SCL2: J13.2, J18.4, R33.1, U16.42, U19.7, U20.4, U21.P13
IO42/SCL3: J19.2, J24.4, R46.1, U23.42, U26.7, U27.4, U28.P13
IO42/SCL4: J25.2, J30.4, R59.1, U30.42, U33.7, U34.4, U35.P13
IO42/SCL5: J31.2, J36.4, R72.1, U37.42, U40.7, U41.4, U42.P13
IO42/SCL6: J37.2, J42.4, R85.1, U44.42, U47.7, U48.4, U49.P13
IO42/SCL7: J43.2, J48.4, R98.1, U51.42, U54.7, U55.4, U56.P13
IO42/SCL8: J49.2, J54.4, R111.1, U58.42, U61.7, U62.4, U63.P13
IO42/SCL9: J55.2, J60.4, R124.1, U65.42, U68.7, U69.4, U70.P13
IO43/SDA: J2.1, J6.3, R7.1, U2.43, U5.8, U6.P14, U7.3
IO43/SDA1: J7.1, J12.3, R21.1, U9.43, U12.8, U13.3, U14.P14
IO43/SDA2: J13.1, J18.3, R34.1, U16.43, U19.8, U20.3, U21.P14
IO43/SDA3: J19.1, J24.3, R47.1, U23.43, U26.8, U27.3, U28.P14
IO43/SDA4: J25.1, J30.3, R60.1, U30.43, U33.8, U34.3, U35.P14
IO43/SDA5: J31.1, J36.3, R73.1, U37.43, U40.8, U41.3, U42.P14
IO43/SDA6: J37.1, J42.3, R86.1, U44.43, U47.8, U48.3, U49.P14
IO43/SDA7: J43.1, J48.3, R99.1, U51.43, U54.8, U55.3, U56.P14
IO43/SDA8: J49.1, J54.3, R112.1, U58.43, U61.8, U62.3, U63.P14
IO43/SDA9: J55.1, J60.3, R125.1, U65.43, U68.8, U69.3, U70.P14
IO44/GPIO0: J2.9, U2.44
IO44/GPIO1: J7.9, U9.44
IO44/GPIO2: J13.9, U16.44
IO44/GPIO3: J19.9, U23.44
IO44/GPIO4: J25.9, U30.44
IO44/GPIO5: J31.9, U37.44
IO44/GPIO6: J37.9, U44.44
IO44/GPIO7: J43.9, U51.44
IO44/GPIO8: J49.9, U58.44
IO44/GPIO9: J55.9, U65.44
IO48/POCI: J2.16, J4.7, U2.48
IO48/POCI1: J7.16, J10.7, U9.48
IO48/POCI2: J13.16, J16.7, U16.48
IO48/POCI3: J19.16, J22.7, U23.48
IO48/POCI4: J25.16, J28.7, U30.48
IO48/POCI5: J31.16, J34.7, U37.48
IO48/POCI6: J37.16, J40.7, U44.48
IO48/POCI7: J43.16, J46.7, U51.48
IO48/POCI8: J49.16, J52.7, U58.48
IO48/POCI9: J55.16, J58.7, U65.48
IO50/PICO: J2.17, J4.3, U2.50
IO50/PICO1: J7.17, J10.3, U9.50
IO50/PICO2: J13.17, J16.3, U16.50
IO50/PICO3: J19.17, J22.3, U23.50
IO50/PICO4: J25.17, J28.3, U30.50
IO50/PICO5: J31.17, J34.3, U37.50
IO50/PICO6: J37.17, J40.3, U44.50
IO50/PICO7: J43.17, J46.3, U51.50
IO50/PICO8: J49.17, J52.3, U58.50
IO50/PICO9: J55.17, J58.3, U65.50
IO51/SD_!CS!: J4.2, TP3.1, U2.51
IO51/SD_!CS!1: J10.2, TP5.1, U9.51
IO51/SD_!CS!2: J16.2, TP15.1, U16.51
IO51/SD_!CS!3: J22.2, TP22.1, U23.51
IO51/SD_!CS!4: J28.2, TP29.1, U30.51
IO51/SD_!CS!5: J34.2, TP36.1, U37.51
IO51/SD_!CS!6: J40.2, TP43.1, U44.51
IO51/SD_!CS!7: J46.2, TP50.1, U51.51
IO51/SD_!CS!8: J52.2, TP57.1, U58.51
IO51/SD_!CS!9: J58.2, TP64.1, U65.51
IO52/SCK: J2.18, J4.5, U2.52
IO52/SCK1: J7.18, J10.5, U9.52
IO52/SCK2: J13.18, J16.5, U16.52
IO52/SCK3: J19.18, J22.5, U23.52
IO52/SCK4: J25.18, J28.5, U30.52
IO52/SCK5: J31.18, J34.5, U37.52
IO52/SCK6: J37.18, J40.5, U44.52
IO52/SCK7: J43.18, J46.5, U51.52
IO52/SCK8: J49.18, J52.5, U58.52
IO52/SCK9: J55.18, J58.5, U65.52
unnamed: J8.B5, R11.2
unnamed: J1.B5, R1.2
unnamed: J1.A5, R2.2
unnamed: D5.A, R9.1
unnamed: D5.C, U4.1
unnamed: R10.2, U4.5
unnamed: J8.A5, R12.2
unnamed: CHG.1, R9.2
unnamed: D6.C, U10.1
unnamed: D4.A, R8.1
unnamed: PWR.1, R8.2
unnamed: D3.C, MEAS.1, MEAS.3, Q1.2
unnamed: D6.A, R13.1
unnamed: D1.DO, TP2.1
unnamed: R15.2, U7.2
unnamed: D2.A, R4.2
unnamed: CHG1.1, R13.2
unnamed: R14.2, U6.P12
unnamed: R16.2, U6.P1
unnamed: C4.1, FB1.2, TP1.1, U2.31
unnamed: R17.2, U10.5
unnamed: D8.DO, TP6.1
unnamed: C24.1, FB2.2, TP14.1, U9.31
unnamed: D9.A, R22.2
unnamed: R23.2, U13.2
unnamed: R24.2, U14.P12
unnamed: R25.2, U14.P1
unnamed: PWR1.1, R26.2
unnamed: D10.A, R26.1
unnamed: D7.C, MEAS1.1, MEAS1.3, Q2.2
unnamed: J14.B5, R27.2
unnamed: J14.A5, R28.2
unnamed: D11.C, U17.1
unnamed: D11.A, R29.1
unnamed: CHG2.1, R29.2
unnamed: R30.2, U17.5
unnamed: D13.DO, TP16.1
unnamed: C40.1, FB3.2, TP21.1, U16.31
unnamed: D14.A, R35.2
unnamed: R36.2, U20.2
unnamed: R37.2, U21.P12
unnamed: R38.2, U21.P1
unnamed: PWR2.1, R39.2
unnamed: D15.A, R39.1
unnamed: D12.C, MEAS2.1, MEAS2.3, Q3.2
unnamed: J20.B5, R40.2
unnamed: J20.A5, R41.2
unnamed: D16.C, U24.1
unnamed: D16.A, R42.1
unnamed: CHG3.1, R42.2
unnamed: R43.2, U24.5
unnamed: D18.DO, TP23.1
unnamed: C56.1, FB4.2, TP28.1, U23.31
unnamed: D19.A, R48.2
unnamed: R49.2, U27.2
unnamed: R50.2, U28.P12
unnamed: R51.2, U28.P1
unnamed: PWR3.1, R52.2
unnamed: D20.A, R52.1
unnamed: D17.C, MEAS3.1, MEAS3.3, Q4.2
unnamed: J26.B5, R53.2
unnamed: J26.A5, R54.2
unnamed: D21.C, U31.1
unnamed: D21.A, R55.1
unnamed: CHG4.1, R55.2
unnamed: R56.2, U31.5
unnamed: D23.DO, TP30.1
unnamed: C72.1, FB5.2, TP35.1, U30.31
unnamed: D24.A, R61.2
unnamed: R62.2, U34.2
unnamed: R63.2, U35.P12
unnamed: R64.2, U35.P1
unnamed: PWR4.1, R65.2
unnamed: D25.A, R65.1
unnamed: D22.C, MEAS4.1, MEAS4.3, Q5.2
unnamed: J32.B5, R66.2
unnamed: J32.A5, R67.2
unnamed: D26.C, U38.1
unnamed: D26.A, R68.1
unnamed: CHG5.1, R68.2
unnamed: R69.2, U38.5
unnamed: D28.DO, TP37.1
unnamed: C88.1, FB6.2, TP42.1, U37.31
unnamed: D29.A, R74.2
unnamed: R75.2, U41.2
unnamed: R76.2, U42.P12
unnamed: R77.2, U42.P1
unnamed: PWR5.1, R78.2
unnamed: D30.A, R78.1
unnamed: D27.C, MEAS5.1, MEAS5.3, Q6.2
unnamed: J38.B5, R79.2
unnamed: J38.A5, R80.2
unnamed: D31.C, U45.1
unnamed: D31.A, R81.1
unnamed: CHG6.1, R81.2
unnamed: R82.2, U45.5
unnamed: D33.DO, TP44.1
unnamed: C104.1, FB7.2, TP49.1, U44.31
unnamed: D34.A, R87.2
unnamed: R88.2, U48.2
unnamed: R89.2, U49.P12
unnamed: R90.2, U49.P1
unnamed: PWR6.1, R91.2
unnamed: D35.A, R91.1
unnamed: D32.C, MEAS6.1, MEAS6.3, Q7.2
unnamed: J44.B5, R92.2
unnamed: J44.A5, R93.2
unnamed: D36.C, U52.1
unnamed: D36.A, R94.1
unnamed: CHG7.1, R94.2
unnamed: R95.2, U52.5
unnamed: D38.DO, TP51.1
unnamed: C120.1, FB8.2, TP56.1, U51.31
unnamed: D39.A, R100.2
unnamed: R101.2, U55.2
unnamed: R102.2, U56.P12
unnamed: R103.2, U56.P1
unnamed: PWR7.1, R104.2
unnamed: D40.A, R104.1
unnamed: D37.C, MEAS7.1, MEAS7.3, Q8.2
unnamed: J50.B5, R105.2
unnamed: J50.A5, R106.2
unnamed: D41.C, U59.1
unnamed: D41.A, R107.1
unnamed: CHG8.1, R107.2
unnamed: R108.2, U59.5
unnamed: D43.DO, TP58.1
unnamed: C136.1, FB9.2, TP63.1, U58.31
unnamed: D44.A, R113.2
unnamed: R114.2, U62.2
unnamed: R115.2, U63.P12
unnamed: R116.2, U63.P1
unnamed: PWR8.1, R117.2
unnamed: D45.A, R117.1
unnamed: D42.C, MEAS8.1, MEAS8.3, Q9.2
unnamed: J56.B5, R118.2
unnamed: J56.A5, R119.2
unnamed: D46.C, U66.1
unnamed: D46.A, R120.1
unnamed: CHG9.1, R120.2
unnamed: R121.2, U66.5
unnamed: D48.DO, TP65.1
unnamed: C152.1, FB10.2, TP70.1, U65.31
unnamed: D49.A, R126.2
unnamed: R127.2, U69.2
unnamed: R128.2, U70.P12
unnamed: R129.2, U70.P1
unnamed: PWR9.1, R130.2
unnamed: D50.A, R130.1
unnamed: D47.C, MEAS9.1, MEAS9.3, Q10.2
SCL_PU_PWR: I2C.3, R5.2
SCL_PU_PWR1: I2C1.3, R20.2
SCL_PU_PWR2: I2C2.3, R33.2
SCL_PU_PWR3: I2C3.3, R46.2
SCL_PU_PWR4: I2C4.3, R59.2
SCL_PU_PWR5: I2C5.3, R72.2
SCL_PU_PWR6: I2C6.3, R85.2
SCL_PU_PWR7: I2C7.3, R98.2
SCL_PU_PWR8: I2C8.3, R111.2
SCL_PU_PWR9: I2C9.3, R124.2
SDA_PU_PWR: I2C.1, R7.2
SDA_PU_PWR1: I2C1.1, R21.2
SDA_PU_PWR2: I2C2.1, R34.2
SDA_PU_PWR3: I2C3.1, R47.2
SDA_PU_PWR4: I2C4.1, R60.2
SDA_PU_PWR5: I2C5.1, R73.2
SDA_PU_PWR6: I2C6.1, R86.2
SDA_PU_PWR7: I2C7.1, R99.2
SDA_PU_PWR8: I2C8.1, R112.2
SDA_PU_PWR9: I2C9.1, R125.2
SHLD: J1.SHLD1, J1.SHLD2, J1.SHLD3, J1.SHLD4, J1.SHLD5, J1.SHLD6, J1.SHLD7, J1.SHLD8, SHLD.2
SHLD1: J8.SHLD1, J8.SHLD2, J8.SHLD3, J8.SHLD4, J8.SHLD5, J8.SHLD6, J8.SHLD7, J8.SHLD8, SHLD1.2
SHLD2: J14.SHLD1, J14.SHLD2, J14.SHLD3, J14.SHLD4, J14.SHLD5, J14.SHLD6, J14.SHLD7, J14.SHLD8, SHLD2.2
SHLD3: J20.SHLD1, J20.SHLD2, J20.SHLD3, J20.SHLD4, J20.SHLD5, J20.SHLD6, J20.SHLD7, J20.SHLD8, SHLD3.2
SHLD4: J26.SHLD1, J26.SHLD2, J26.SHLD3, J26.SHLD4, J26.SHLD5, J26.SHLD6, J26.SHLD7, J26.SHLD8, SHLD4.2
SHLD5: J32.SHLD1, J32.SHLD2, J32.SHLD3, J32.SHLD4, J32.SHLD5, J32.SHLD6, J32.SHLD7, J32.SHLD8, SHLD5.2
SHLD6: J38.SHLD1, J38.SHLD2, J38.SHLD3, J38.SHLD4, J38.SHLD5, J38.SHLD6, J38.SHLD7, J38.SHLD8, SHLD6.2
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
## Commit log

2022-08-08 Initial commit.
2022-08-11 First draft schematic, initial pcb layout.
2022-08-15 Updates in prep for sch review
    Schematic: Replaced 0603 10ks with 0402T package.
    Board: Initial layout of parts complete.
2022-08-15 Changed package of 100R, rearrange board.
    Changed 100R from 0603 to 0402T and rearranged the board to better organize that circuit. Also moved the QWIIC logo next to the QWIIC connector with the new space.
2022-08-15 Added net classing, net names.
2022-08-15 Update netclasses and board thickness.
2022-08-15 Routed high speed and analog.
2022-08-19 Routing, end of week commit.
2022-08-31 routed and ready for v01 design review.
2022-09-06 v01 ready for production.
    Move Power LED
    Move MEAS jumper
    Move GPIO6 to a new IO pin
    Remove Q2
    Allow ground pour between IO41 and SDA
    Add vias next to BME280 ground pad
2022-10-24 Added datasheets.
2022-11-29 Added examples.
2022-11-29 Remove bad example. There's no DAC.
2022-12-12 Update for v10 post-proto changes.
    Add CHG LED silk
    Flip silk text direction on rear !RST!
    Change GPIO6/IO35 silk
    Add silk for first pin on SWD pogo
    Re-place updated ESD diode.
2022-12-19 Added Layer numbers
2022-12-19 Moved files to proper spot.
2023-02-09 Modified verification test scripts to work with the new BSP.
2023-03-04 Start BLE library, add LICENSE/library.properties.
2023-03-04 Add wrapper classes for sensors to map to Adafruit_Sensor class.
2023-03-04 Add SparkFunBLE Sensor Services for onboard devices.
2023-03-04 WIP Create Data pipe example.
2023-03-07 Update library.properties file.
2023-03-07 Remove RGB file since no longer being used.
2023-03-07 Refactor IMU sensor service. Rolls ACC/GYRO into one service creates two instances of Wrapper class. Both wrappers point to the same sensor, but different sensors.
2023-03-07 Refactor ENV sensor. Provides one BLE service that creates 3 instances of a wrapper. Each wrapper points to one aspect of the same sensor.
2023-03-08 Update ISM330DHCX Wrapper
    Set consts to constexprs.
    Make _sensor data an object instead of a pointer.
    Have type be an enum instead of a bool.
    Add missing function types for getEvent and getSensor.
    Pointer fun.
2023-03-08 Update BME280 Wrapper
    Refactor class so it no longer requires envData object.
    Retyped const to constexpr.
    Changed save data to direct storage in event variable.
    Renamed bad variables.
    Added missing function types for getEvent and getSensor.
2023-03-08 Added missing header to generic Sensor header.
2023-03-08 Update IMU BLE Service.
    Added correct headers.
    Changed name of data UUID.
    Swapped Adafruit_Sensor to Wrapper class.
    Added objects so they aren't there temporarily.
    Pointer fun.
2023-03-08 Update BME280 BLE Service
    Added missing headers.
    Removed readSensor function, it's now done inside the wrapper.
    Removed the need to have a pointer to sensor measurements at this level.
    Moved Adafruit_Sensor pointers to the correct Wrapper class.
    Removed sensor measurement pointer.
    Added Wrapper objects.
2023-03-10 Create README.md
    Creating README.md with photos/links.
2023-03-14 Wrappers have serial now.
2023-03-14 Services have serial now.
2023-03-14 WIP example, update.
2023-03-20 Update Example01_BLE_Data_Pipe.ino
    Removed Serial print statements.
    Removed old unused code.
    Added Service Advertising.
    Added Battery update check.
2023-03-20 Update ISM wrapper
    Removed print statements.
    Reformatted code.
2023-03-20 Update BME wrapper
    Removed print statements.
    Reformatted code.
2023-03-20 Update SparkFunBLE_Sensor.cpp
    reformat code.
2023-03-20 Update ISM service.
    Reformat code.
    Removed print statements.
    Modified measure handler to properly post data.
    Added callbacks.
2023-03-20 Update BME Service.
    Reformat code.
    Removed print statements.
    Modified measure handler to properly post data.
    Added callbacks.
2023-03-22 Update example, update Readme
    Remove serial gate.
    Add a readme.
2023-03-23 Moved library to board repo so it's automatically included. Updated readme.
